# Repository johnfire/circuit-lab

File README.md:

# circuit-lab

AI-assisted electronic circuit design for Raspberry Pi and other embedded
projects — analog **and** digital — powered by a headless **ngspice** engine
driven from a small Python harness.

> **Documentation:** [`HOW-TO.md`](HOW-TO.md) is the full guide, written for
> **both humans and AI agents** (the agent section covers the netlist
> conventions and verification steps to follow).

## Layout

```
circuit-lab/
  backend/               # local FastAPI catalog, bounded simulation workers, checks
  frontend/              # React/TypeScript workbench and browser regressions
  harness/
    run_circuit.py        # ngspice driver: netlist -> parsed results (op/data) + plots
  circuits/
    analog/               # R/C/L, dividers, MOSFET switches, LED, op-amp, level shifter
    digital/              # behavioral + (where used) XSPICE digital logic
  README.md
```

## Requirements

- Linux. ngspice 47 is a self-contained, no-sudo install under `~/.local`
  (built headless: `--with-x=no --enable-xspice`), so it needs no X11 and no
  root. `~/.local/bin` must be on `PATH`.
- Python 3 + optional `matplotlib` for `--plot`.

## Web prototype

The first workbench supports local and gated hosted modes: nine recipes, editable resistor/capacitor
values, real ngspice waveforms with zoom/cursor measurements, numerical checks,
a supported-component connectivity table, netlist inspection, and JSON export.
It does not yet have AI chat, schematic editing, or persistent saved designs.

The web prototype needs Python 3.12+, uv, and Node.js 26/npm, in addition to
ngspice. Locked Python and npm dependencies are committed.
From the repository root:

    uv sync --frozen --all-extras
    npm ci --prefix frontend
    npm run build --prefix frontend
    uv run uvicorn backend.application:app --host 127.0.0.1 --port 8010

Open http://127.0.0.1:8010 on this computer. This is not a public/mobile-hosted
deployment; do not bind it to the network or put an unauthenticated proxy in
front of it. Development mode: run the API above, then run the following
in another terminal:

    npm run dev --prefix frontend

All models are marked generic/ideal. Passing checks are not hardware approval,
component-rating verification, or permission to connect a Raspberry Pi.
The API accepts only registered recipes and bounded numeric overrides, not
arbitrary netlists. Each job has its own temporary directory and process group,
resource limits, timeouts, and a two-worker ceiling. Hosted mode uses the
network-isolated worker described in [the deployment runbook](deploy/README.md).

Run the same checks used by CI:

    uv run ruff check backend harness tests
    uv run mypy backend
    uv run pytest --cov=backend --cov=harness --cov-report=term-missing --cov-fail-under=70
    npm run lint --prefix frontend
    npm run build --prefix frontend
    cd frontend
    npx playwright install chromium
    npm run test:e2e

Simulation events are appended to /tmp/circuit-lab-audit.jsonl, with correlation
IDs and the local-user actor. Set CIRCUIT_AUDIT_PATH for a different local
destination. Missing audit storage rejects jobs without breaking the catalog.
Local mode has no accounts. Hosted mode requires a trusted gateway and records
its authenticated identity on simulation events. Hosted mode has a public signup
landing page and self-hosted Keycloak accounts; see [deployment runbook](deploy/README.md).
See [prototype status](docs/prototype-status.md) for scope and next milestones.

The MCP interface now supports explicitly shared saved projects and browser
workspaces, revision-safe AI editing with undo, and real transient/AC evidence.
It uses a separate application PostgreSQL database and verified Keycloak OAuth;
without those dependencies, local drafts and the existing simulator still work.
Production activation and actual Codex linking are not completed by the local
build. See [MCP implementation status](docs/mcp-implementation-status.md) and the
[activation runbook](deploy/MCP.md) for the tested boundaries and rollout gates.

## Command-line quick start

```bash
# list example circuits
python3 harness/run_circuit.py list

# run a circuit and print its operating point / data tables
python3 harness/run_circuit.py run circuits/analog/voltage_divider.cir

# run with parameter substitutes
python3 harness/run_circuit.py run circuits/analog/rc_lowpass.cir --set R1=4700

# sweep a parameter (runs ngspice once per value)
python3 harness/run_circuit.py run circuits/analog/rc_lowpass.cir --sweep R1=4700,10000,22000

# render a plot of the first data CSV
python3 harness/run_circuit.py run circuits/analog/rc_lowpass.cir --plot /tmp/rc.png

# scaffold a new circuit
python3 harness/run_circuit.py new circuits/analog/my_circuit
```

## Netlist conventions (important for reliable parsing)

The harness reads results two ways:

1. **Operating-point / printed scalars** — any
   `v(node) = value` lines in the log (from `print v(x)` after `op`, `dc`,
   or `tran`) are reported as `v(node) = value`.
2. **Data tables** — every `*.csv` written by `wrdata` in the netlist's
   `.control` block. ngspice's `wrdata` is finicky: **pass ONE vector per
   call** (a single-vector `wrdata` yields a clean 2-column CSV
   `[abscissa, value]`). Passing several vectors to one call interleaves the
   abscissa and is unusable. So a typical `.control` block is:

```
.control
tran 0.01m 80m           # or: dc VIN 0 5 0.5   |  ac dec 10 1 1meg
wrdata v_in.csv v(in)     # one signal per file
wrdata v_out.csv v(out)
.endc
.end
```

`wrdata` writes relative to the ngspice working directory, which the harness
owns; your netlist should use plain relative filenames.

## Adding a circuit

1. Write a `.cir` netlist. Use the `.control` block for the analysis and one
   `wrdata` per signal you care about.
2. Reuse these building blocks:
   - **Analog**: R/C/L, V/I sources (DC `V in 0 5`, `PULSE(v1 v2 td tr tf pw per)`),
     diodes `D ... <model>`, MOSFETs `M <d g s b> <model>`, and a portable
     behavioral op-amp subcircuit (see `opamp_noninv.cir`).
   - **Digital**: behavioral logic via `B` sources, e.g. an inverter
     `B1 out 0 V = 3.3*(V(in)<1.65)`, a NAND
     `... V = 3.3*((V(a)<1.65)|(V(b)<1.65))`. XSPICE digital primitives
     (`a1 ...`) are also available when the exact gate model is wanted.

## Parts library

Real diodes, LEDs, Zeners, MOSFETs, BJTs, op-amps and linear regulators for the schematic editor
and MCP clients live in `circuits/parts/<category>/<id>/part.json`: structured model parameters
(our code writes the `.model` line, or a behavioral `.subckt` for op-amps and regulators),
absolute-maximum ratings, characterization tests, and a trust record. Every transient run checks
each library part against its ratings on the solver's own timepoints.

Development boards (Raspberry Pi 4 and 5, Pi Pico, Arduino Uno R3, ESP32-DevKitC) live in
`circuits/boards/<id>/board.json`: the full header pinout plus pin-level electrical limits. A
"Board pin" part places one header pin as an output, pulse, input or supply. It's modelled with
drive resistance, pulls and ESD clamp diodes, and checked for pin current, overvoltage (5 V into a
Pi) and supply budgets. Firmware is not simulated.

The circuit library (`circuits/blocks/<id>.json`) holds curated building blocks: LED on a Pi pin,
NPN switch, relay driver, 5 V → Pi divider, BSS138 level shifter, PWM filter, op-amp follower and
gain stage, and LM1117/7805 supplies. Each is a complete circuit with stated expectations ("LED
current about 3.6 mA"); CI simulates every block and requires its expectations and every part rating
to pass. The browser can insert a block beside your circuit or open it; MCP clients use
`list_circuit_blocks`, `get_circuit_block` and the `insert_block` edit.

```bash
uv run python -m backend.parts_cli list                           # parts and trust level
uv run python -m backend.parts_cli verify [ids...]                # characterization on real ngspice
uv run python -m backend.parts_cli new mosfet/irf3708 --kind NMOS # scaffold part.draft.json
uv run python -m backend.parts_cli index                          # regenerate the parts, boards and blocks indexes
```

Adding a part:
1. Scaffold it, fill in the draft, and rename it to `part.json`.
2. Run `verify`.
3. Run `index`, which CI checks is current.

A part becomes `verified` only after a named human checks every value against the datasheet. The
loader rejects `verified` unless the file has a datasheet URL, `datasheet p.N` citations on every
rating and test, a reviewer and a date. All starter parts are currently drafts.

## Ordering a PCB (via KiCad)

Circuit Lab doesn't lay out boards; it hands KiCad a correct netlist. "Export for PCB (KiCad)" (or
the MCP tool `export_kicad_files`) produces:

- `circuit-lab.net`, which you import into KiCad's PCB editor (File → Import → Netlist). Every part
  arrives with its chosen footprint and nets. Sources become 2-pin input headers; Raspberry Pi pins
  land on a 2×20 socket at their real header positions, with all Pi GND pins on ground; other boards'
  pins become labelled wire pads.
- `circuit-lab-bom.csv`, in JLCPCB's columns (Comment, Designator, Footprint, LCSC Part #).

Each part picks a footprint in its properties (through-hole or SMD where offered). Every footprint
name is in `circuits/kicad-footprints-verified.txt`, checked against KiCad's official library, and
CI refuses unchecked names. Pin-to-pad maps for library parts are **drafts**: check each against the
datasheet's package drawing. LCSC numbers are left empty until confirmed. In KiCad: place, route,
run DRC, then plot Gerbers and drill files and upload them to JLCPCB or PCBWay.

## Notes / pitfalls

- `op ; print v(x)` can return stale/zero values if the engine isn't fully
  initialised; prefer `dc`, `tran`, or `ac` plus `wrdata` for guaranteed data.
- The earlier "Arch package extracted to `~/.local`" shortcut is **not** used
  here: that binary hardcodes `/usr/lib/ngspice` code models and returns
  all-zero simulations when it can't find them. The harness uses the
  self-built headless ngspice 47 instead.
- Sweeps use the source **name** (`dc VIN 0 5 1`), not the node (`dc v(in)...`).

## Languages

The landing page, workbench, readable downloads and account flows support German
and English. First visits follow browser language preferences; unsupported
languages fall back to English. Use the top selector to remember another choice.
Circuit identifiers and machine-readable formats stay unchanged. See
[localization](docs/localization.md) for translation sources and verification, and
the [deployment runbook](deploy/README.md) for the separate identity migration.

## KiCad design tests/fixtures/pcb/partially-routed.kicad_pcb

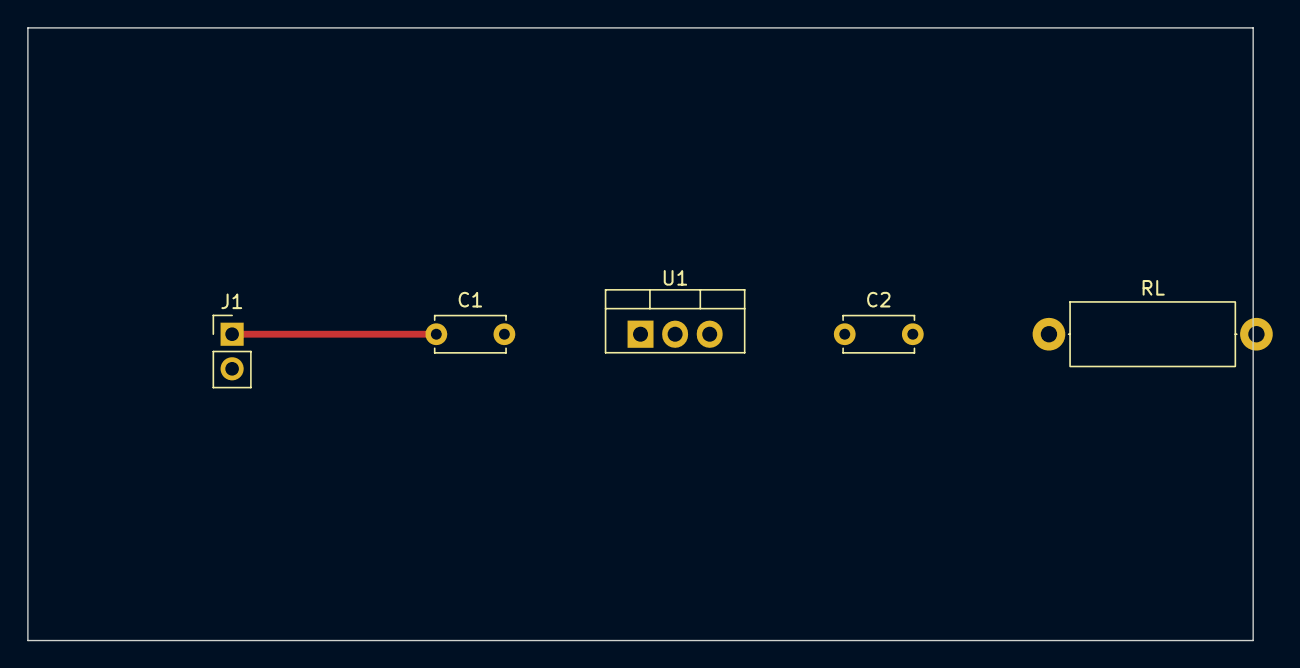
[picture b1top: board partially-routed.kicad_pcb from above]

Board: 2 copper layers, 90.0 x 45.0 mm, 5 parts (0 on the bottom side), 3 nets.

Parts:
C1: 330nF 50V; C_Disc_D5.0mm_W2.5mm_P5.00mm
C2: 100nF 50V; C_Disc_D5.0mm_W2.5mm_P5.00mm
J1: VIN input; PinHeader_1x02_P2.54mm_Vertical
RL: 50; R_Axial_DIN0414_L11.9mm_D4.5mm_P15.24mm_Horizontal
U1: LM7805; TO-220-3_Vertical

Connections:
/GND: C1.2, C2.2, J1.2, RL.2, U1.2
/N0: C1.1, J1.1, U1.1
/N2: C2.1, RL.1, U1.3
